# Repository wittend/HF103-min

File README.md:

# HF103-min
A minimalist re-implementation of Oscar Stella's HF-103 work

Possibly to be renamed ClementineSDR.  Currently just a KiCad capture of parts of Oskar Stella's HF-103/BBRF-103 projects.  This is intended to assist in prototyping for the HamSCI/TAPR receiver atmospheric phenomena.  Will be coupled with a GPSDO design TBD.  

For use in the HamSCI Personal Space Weather Station (PSWS) project.

For more info, see https://hamsci.org and https://tangerinesdr.com.

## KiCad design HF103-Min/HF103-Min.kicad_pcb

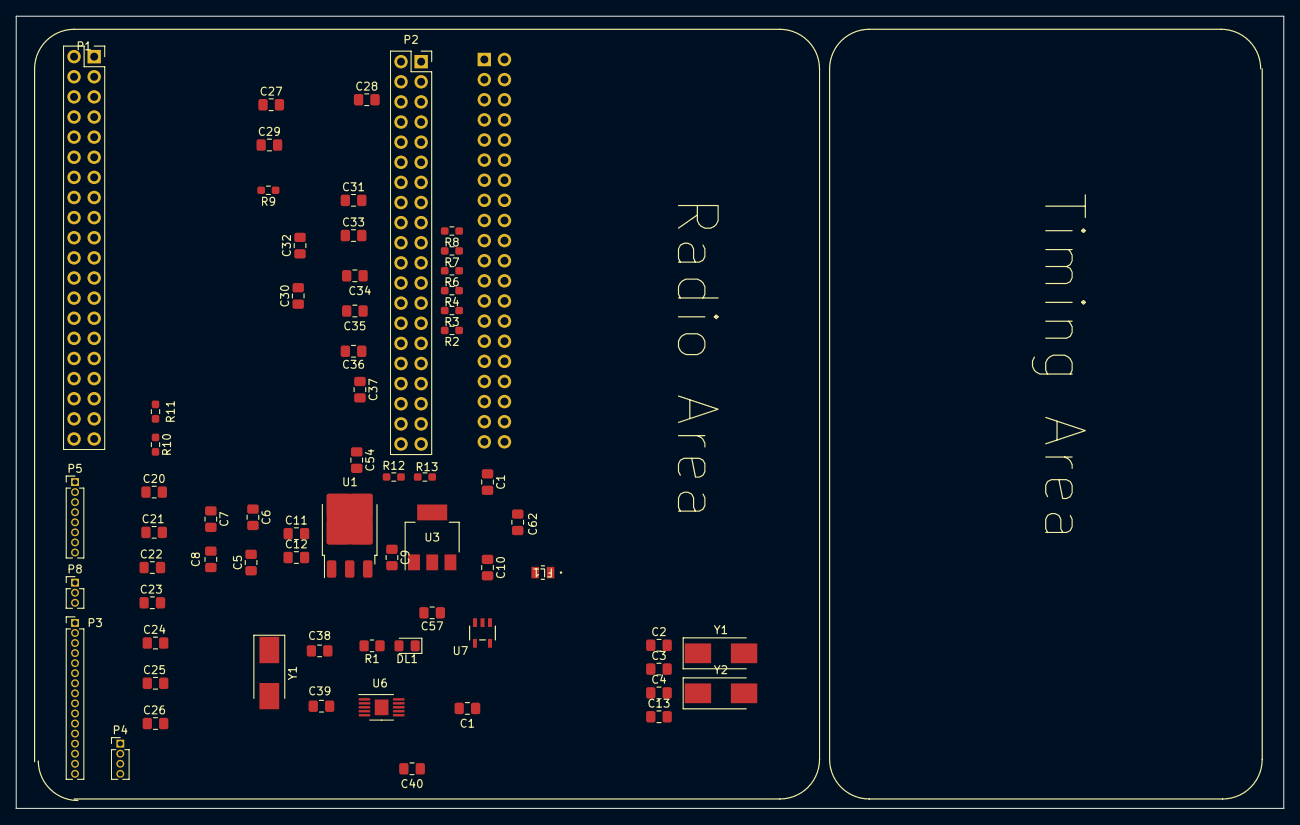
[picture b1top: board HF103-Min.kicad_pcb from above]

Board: 4 copper layers, 160.0 x 100.0 mm, 66 parts (1 on the bottom side), 48 nets, no tracks yet.

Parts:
C1, C1#2: 0.1uF; C_0805_2012Metric_Pad1.18x1.45mm_HandSolder
C2, C3, C4, C13, C38, C39: ? pF; C_0805_2012Metric_Pad1.18x1.45mm_HandSolder
C5, C6, C10, C11: 100nF; C_0805_2012Metric_Pad1.18x1.45mm_HandSolder
C7, C8, C12: 1uF; C_0805_2012Metric_Pad1.18x1.45mm_HandSolder
C9: 10uF; C_0805_2012Metric_Pad1.18x1.45mm_HandSolder
C20, C21, C22, C23, C24, C25, C26, C27, C28, C29, C30, C31, C32, C33, C34, C35, C36, C37, C54: 100pf; C_0805_2012Metric_Pad1.18x1.45mm_HandSolder
C40: 1 nF; C_0805_2012Metric_Pad1.18x1.45mm_HandSolder
C57, C62: 1u; C_0805_2012Metric_Pad1.18x1.45mm_HandSolder
DL1: Power; D_0805_2012Metric_Pad1.15x1.40mm_HandSolder
FL1: MPZ2012S601AT; IND_2012_TDK
J1: 2x20-Odd/Even; PinSocket_2x20_P2.54mm_Horizontal
P1, P2: 2x20-Odd/Even; PinSocket_2x20_P2.54mm_Vertical
P3: Conn_01x16; PinHeader_1x16_P1.27mm_Vertical
P4: Conn_01x04; PinHeader_1x04_P1.27mm_Vertical
P5: Conn_01x08; PinHeader_1x08_P1.27mm_Vertical
P8: Conn_01x03; PinHeader_1x03_P1.27mm_Vertical
R1: 1k2; R_0805_2012Metric_Pad1.20x1.40mm_HandSolder
R2, R4, R6, R7, R8, R9, R10, R11: 1k; R_0603_1608Metric_Pad0.98x0.95mm_HandSolder
R3: 10k; R_0603_1608Metric_Pad0.98x0.95mm_HandSolder
R12, R13: 100; R_0603_1608Metric_Pad0.98x0.95mm_HandSolder
U1: AMS1117CD-1.8; TO-252-3_TabPin2
U3: AP7361C-33E; SOT-223-3_TabPin2
U6: SI5351A-B-GT; MSOP-10-1EP_3x3mm_P0.5mm_EP1.73x1.98mm
U7: NCP360SNT1G; TSOP5_3X1P5_ONS
Y1, Y1#2, Y2: 27 MHz; Crystal_SMD_0603-2Pin_6.0x3.5mm_HandSoldering

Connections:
+1V8: C6.1, C7.1, U1.2 (VO)
+5C: P2.3, P2.4, P3.1, P8.2
ATT CLK: C32.1, P3.7, R6.2
ATT DATA: C31.1, P3.6, R7.2
ATT LE: C33.1, P3.8, R4.2
D0: J1.37, P2.38
D1: J1.35, P2.36
D2: J1.33, P2.34
D3: J1.31, P2.32
D4: J1.29, P2.30
D5: J1.27, P2.28
D6: J1.25, P2.26
D7: J1.23, P2.24
D8: J1.21, P2.22
D9: J1.19, P2.20
D10: J1.17, P2.18
D11: J1.15, P2.16
D12: J1.13, P2.14
D13: J1.11, P2.12
D14: J1.9, P2.10
D15: J1.7, P2.8
GND: C1.2, C1#2.2, C2.1, C3.2, C4.1, C5.2, C6.2, C7.2, C8.2, C9.2, C10.2, C11.2, C12.2, C13.2, C20.1, C21.2, C22.2, C23.2, C24.2, C25.2, C26.2, C27.2, C28.2, C29.2, C30.2, C31.2, C32.2, C33.2, C34.2, C35.2, C36.2, C37.2, C38.1, C39.2, C40.1, C54.1, C57.2, C62.2, DL1.1 (K), FL1.2, J1.2, J1.4, J1.5, J1.6, J1.8, J1.10, J1.12, J1.14, J1.16, J1.18, J1.20, J1.22, J1.24, J1.26, J1.28, J1.30, J1.32, J1.34, J1.36, J1.38, J1.40, P1.39, P1.40, P2.5, P2.6, P2.33, P2.37, P3.11, P3.14, P4.4, P5.1, P8.1, P8.3, U1.1 (GND), U3.2 (GND), U6.8 (GND), U7.2 (GND), U7.3 (*EN)
GPIO19: P2.27, R2.1
GPIO20: P2.25, R3.1
GPIO21: P2.23, R4.1
GPIO22: P2.21, R6.1
GPIO23: P2.19, R7.1
GPIO24: P2.17, R8.1
GPIO25: P2.15, R9.1
GPIO26: P2.13, R10.1
GPIO27: P2.11, R11.1
I2C SCL: P2.40, R12.1, U6.4 (SCL)
I2C SDA: P2.39, R13.1, U6.5 (SDA)
unnamed: DL1.2 (A), R1.1
unnamed: C1#2.1, J1.39
unnamed: C22.1, C27.1, P3.2, P5.3, R11.2
unnamed: C24.1, C28.1, P3.3, P5.4, R10.2
unnamed: C21.1, C29.1, P3.4, P5.5, R9.2
unnamed: C23.1, C25.1, C30.1, C34.1, P3.5, P3.9, P5.6, P5.7, R3.2, R8.2
unnamed: C26.1, C35.1, P3.10, P5.8, R2.2
unnamed: C20.2, C36.1, C37.1, P3.15, P4.1, R13.2
unnamed: C54.2, P3.16, P4.2, R12.2
unnamed: C9.1, C10.1, C62.1, U3.1 (VI), U7.5 (OUT)
unnamed: C40.2, U6.7 (VDDO)
unnamed: C57.1, FL1.1, U7.1 (IN)
VDD: C5.1, C8.1, C11.1, C12.1, R1.2, U1.3 (VI), U3.3 (VO), U6.1 (VDD)
XA: C3.1, C13.1, C39.1, U6.2 (XA), Y1.2, Y1#2.2, Y2.2
XB: C2.2, C4.2, C38.2, U6.3 (XB), Y1.1, Y1#2.1, Y2.1

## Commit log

2023-08-12 Initial file upload
2023-08-12 Second try at uploading files into the correct heirarchy
